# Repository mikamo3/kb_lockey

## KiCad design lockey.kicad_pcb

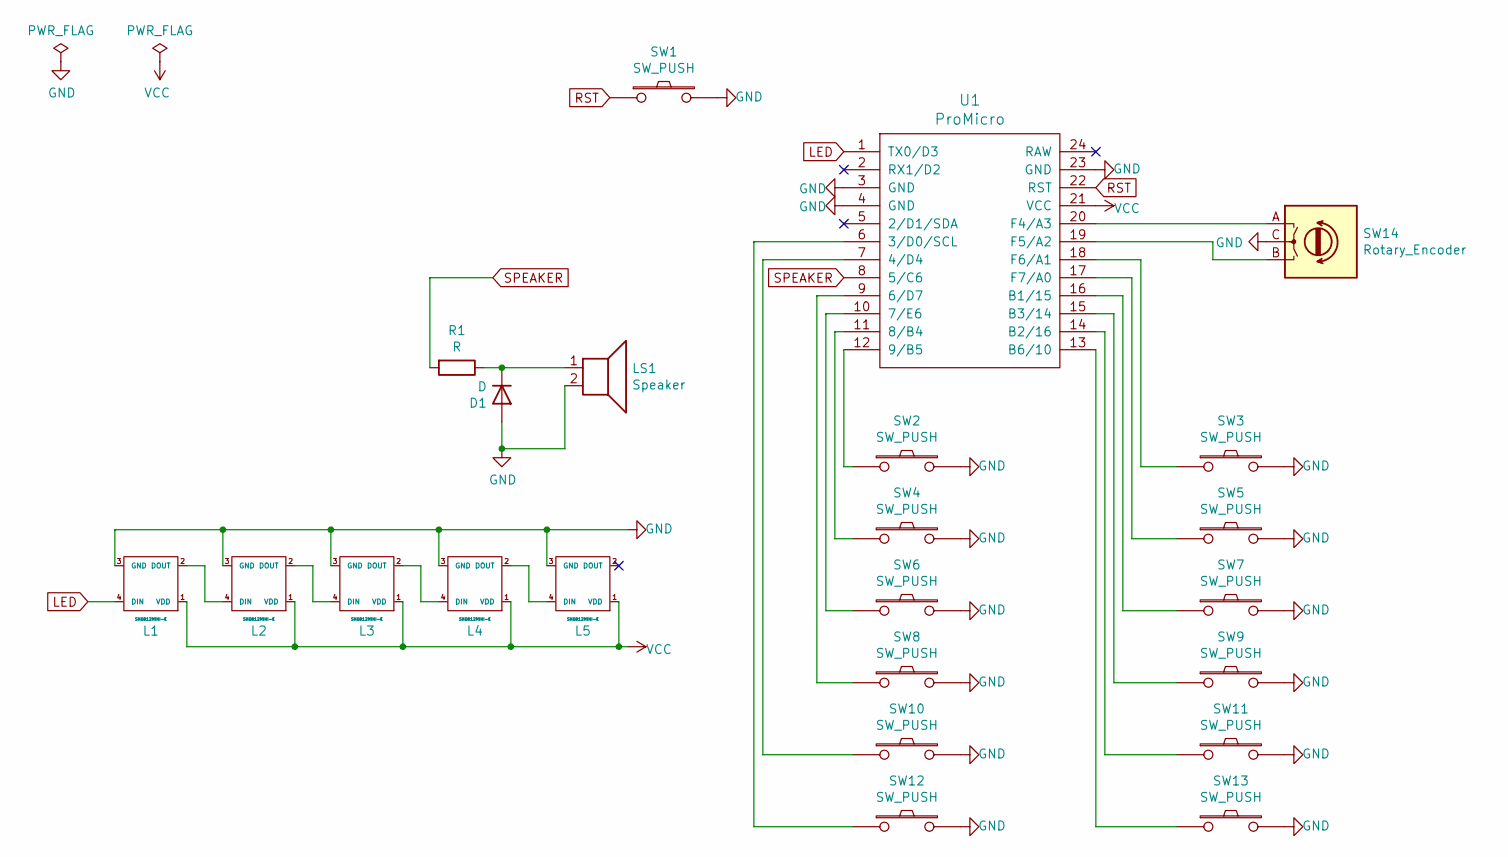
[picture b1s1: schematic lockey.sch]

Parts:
D1: D; D3_TH_SMD
L1, L2, L3, L4, L5: SK6812MINI-E; YS-SK6812MINI-E_front
LS1: Speaker; PKLCS1212E4001_HandSoldering
R1: R; Resistor-Hybrid
SW1: SW_PUSH; ResetSW_1side
SW2, SW3, SW4, SW5, SW6, SW7, SW8, SW9, SW10, SW11, SW12, SW13: SW_PUSH; TactSwitch_1side
SW14: Rotary_Encoder; RotaryEncoder_Alps_EC12E_Vertical_H20mm
U1: ProMicro; ProMicro_v3.5

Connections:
GND: D1.2 (A), L1.3 (GND), L2.3 (GND), L3.3 (GND), L4.3 (GND), L5.3 (GND), LS1.2, SW1.2, SW2.2, SW3.2, SW4.2, SW5.2, SW6.2, SW7.2, SW8.2, SW9.2, SW10.2, SW11.2, SW12.2, SW13.2, SW14.C, U1.3 (GND), U1.4 (GND), U1.23 (GND)
LED: L1.4 (DIN), U1.1 (TX0/D3)
unnamed: D1.1 (K), LS1.1, R1.1
unnamed: L1.2 (DOUT), L2.4 (DIN)
unnamed: L2.2 (DOUT), L3.4 (DIN)
unnamed: L3.2 (DOUT), L4.4 (DIN)
unnamed: L4.2 (DOUT), L5.4 (DIN)
unnamed: SW2.1, U1.12 (9/B5)
unnamed: SW3.1, U1.18 (F6/A1)
unnamed: SW4.1, U1.11 (8/B4)
unnamed: SW5.1, U1.17 (F7/A0)
unnamed: SW6.1, U1.10 (7/E6)
unnamed: SW7.1, U1.16 (B1/15)
unnamed: SW8.1, U1.9 (6/D7)
unnamed: SW9.1, U1.15 (B3/14)
unnamed: SW10.1, U1.7 (4/D4)
unnamed: SW11.1, U1.14 (B2/16)
unnamed: SW12.1, U1.6 (3/D0/SCL)
unnamed: SW13.1, U1.13 (B6/10)
unnamed: SW14.A, U1.20 (F4/A3)
unnamed: SW14.B, U1.19 (F5/A2)
RST: SW1.1, U1.22 (RST)
SPEAKER: R1.2, U1.8 (5/C6)
VCC: L1.1 (VDD), L2.1 (VDD), L3.1 (VDD), L4.1 (VDD), L5.1 (VDD), U1.21 (VCC)

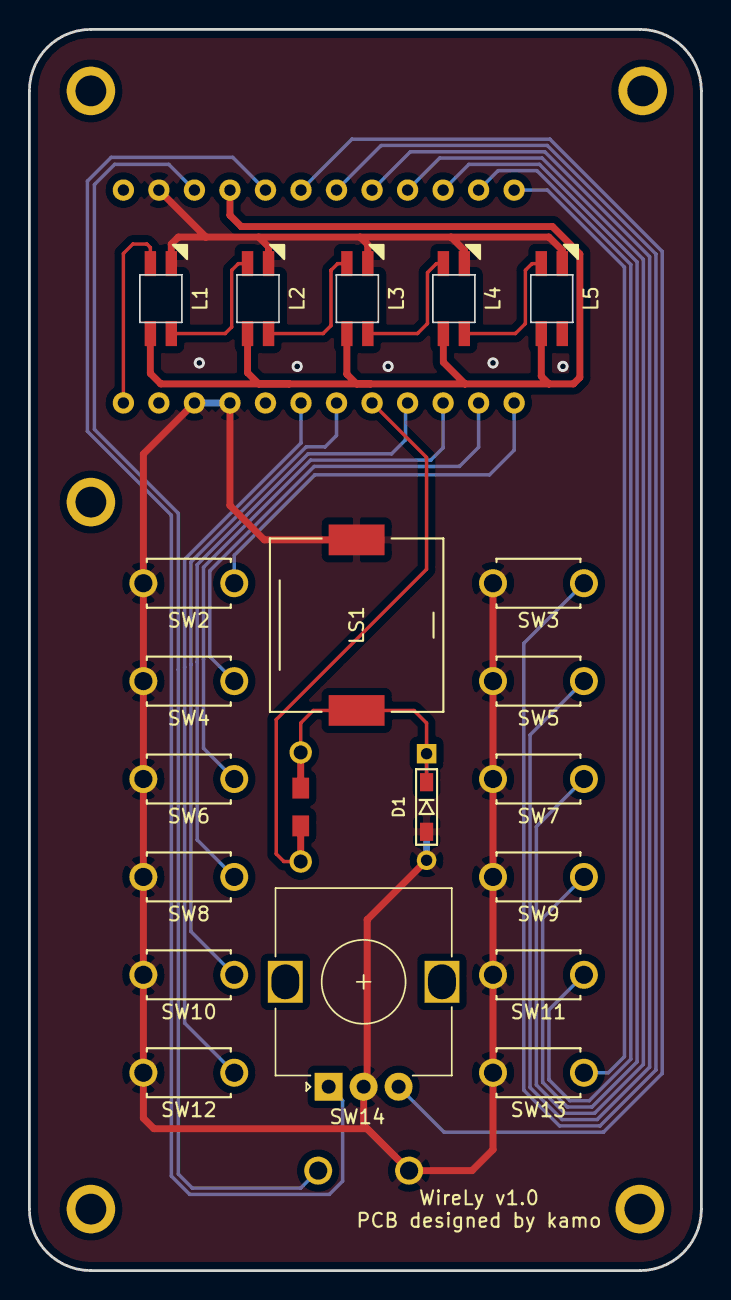
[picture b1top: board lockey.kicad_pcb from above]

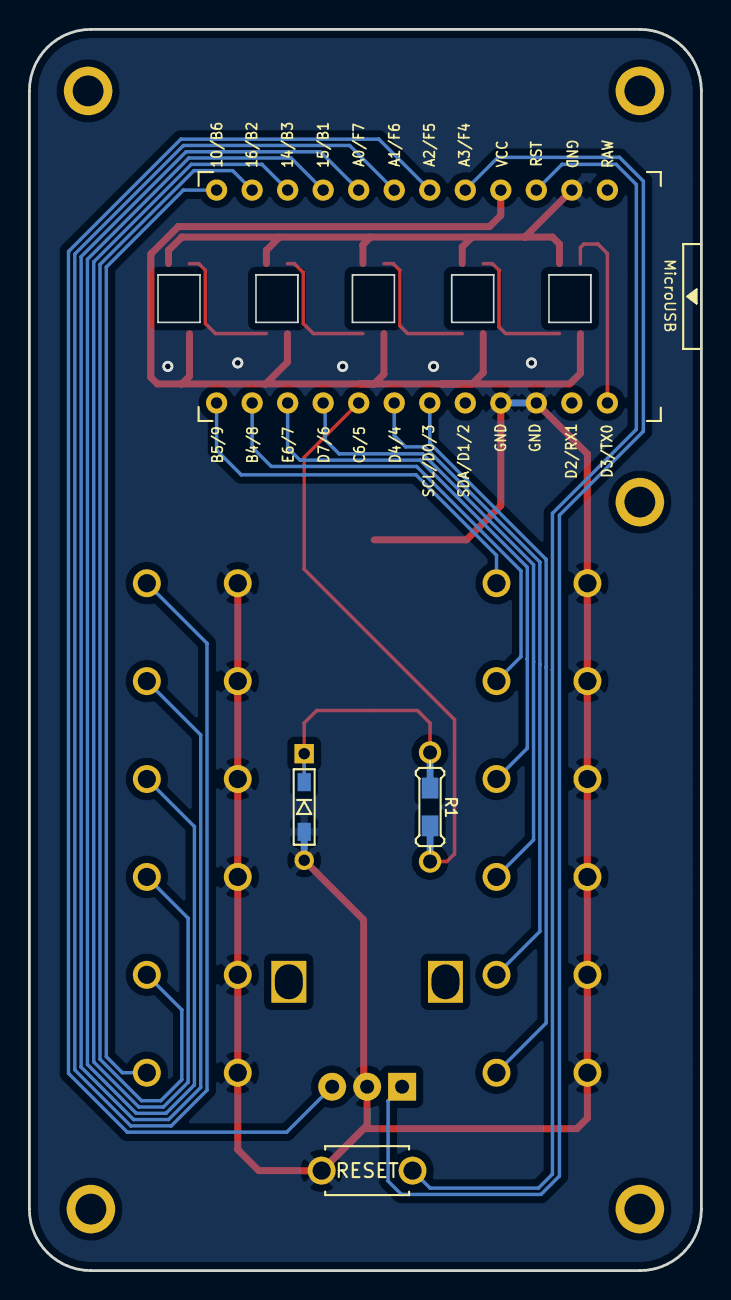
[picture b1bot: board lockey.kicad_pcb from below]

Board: 2 copper layers, 48.1 x 88.8 mm, 28 parts (3 on the bottom side), 24 nets.

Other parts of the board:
J4, J4#2, J4#3, J4#4, J4#5: Conn_01x01; M2hole

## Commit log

2021-05-04 :sparkles: (all) firstcommit
2021-05-04 :page_facing_up: (add)
2021-05-06 :sparkles: (all) create firstversion
2021-05-07 :bug: (case) rename case pcb filename
